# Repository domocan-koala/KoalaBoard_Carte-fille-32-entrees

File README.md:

# Carte fille 32 entrées

/3D_dessus.jpg)

Carte fille compatible [KoalaBoard](https://github.com/domocan-koala/KoalaBoard) pour relier 32 boutons-poussoirs avec votre système domotique [Domocan Master Édition](https://www.abcelectronique.com/bigonoff/forum/forumdisplay.php?fid=22).

## Historique
	
	* 23/02/18 V1.0 : Première version mise en ligne

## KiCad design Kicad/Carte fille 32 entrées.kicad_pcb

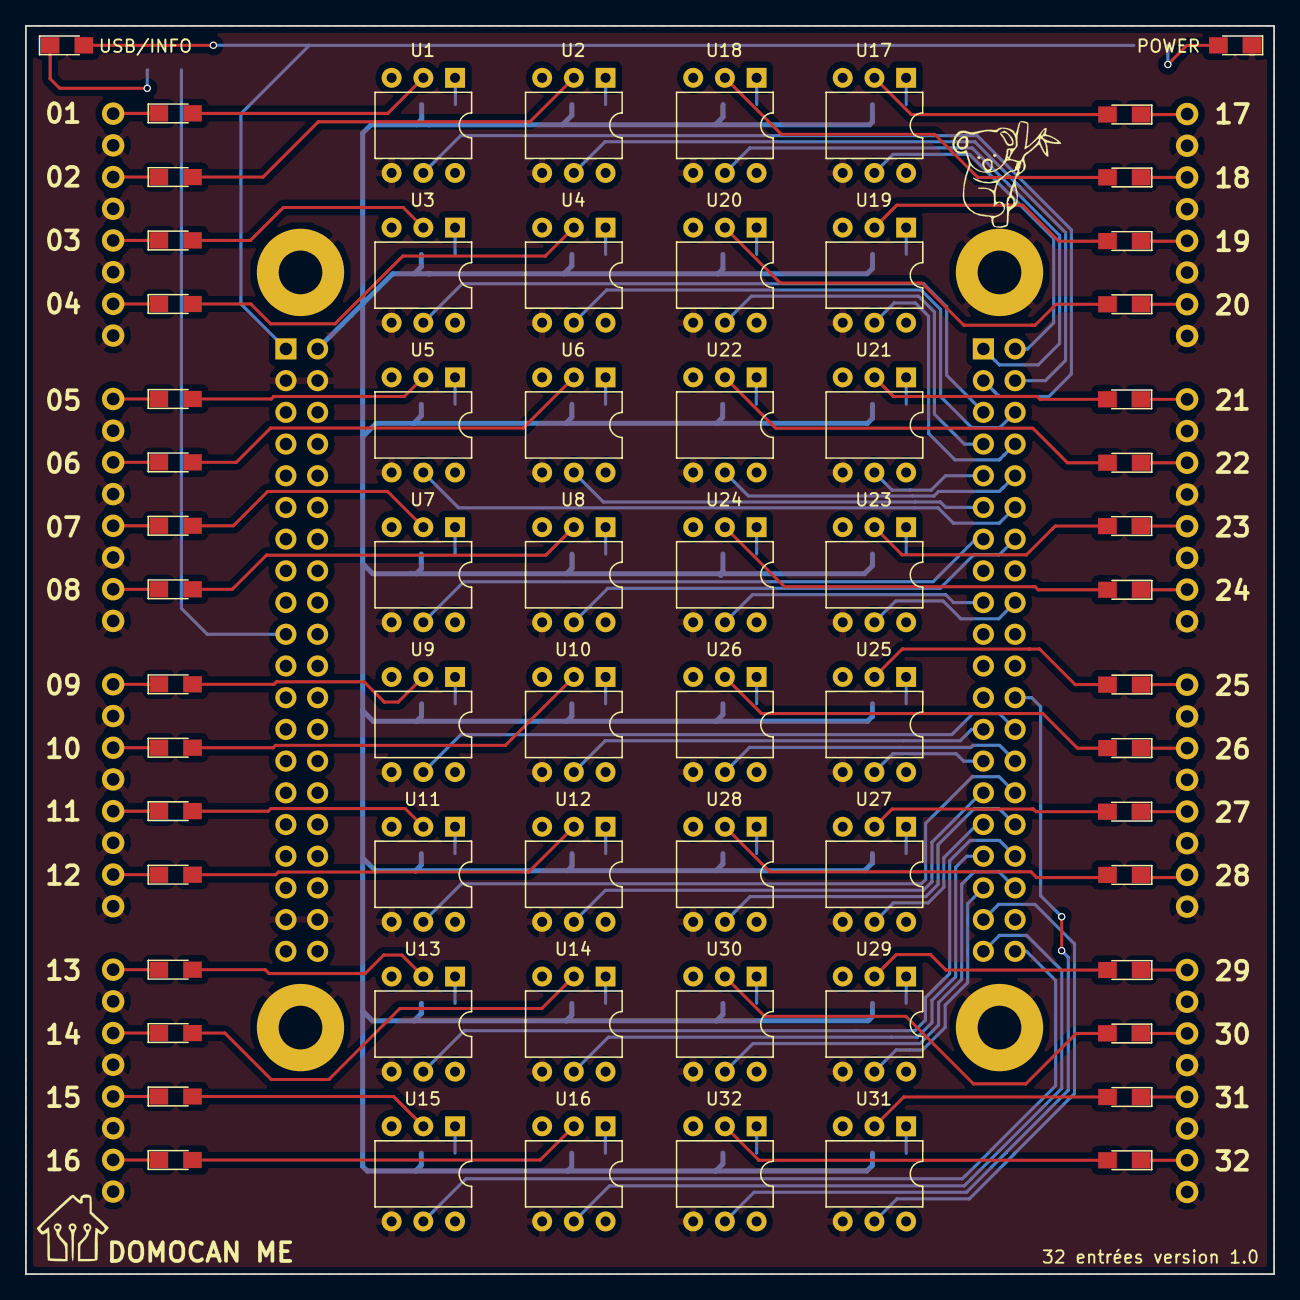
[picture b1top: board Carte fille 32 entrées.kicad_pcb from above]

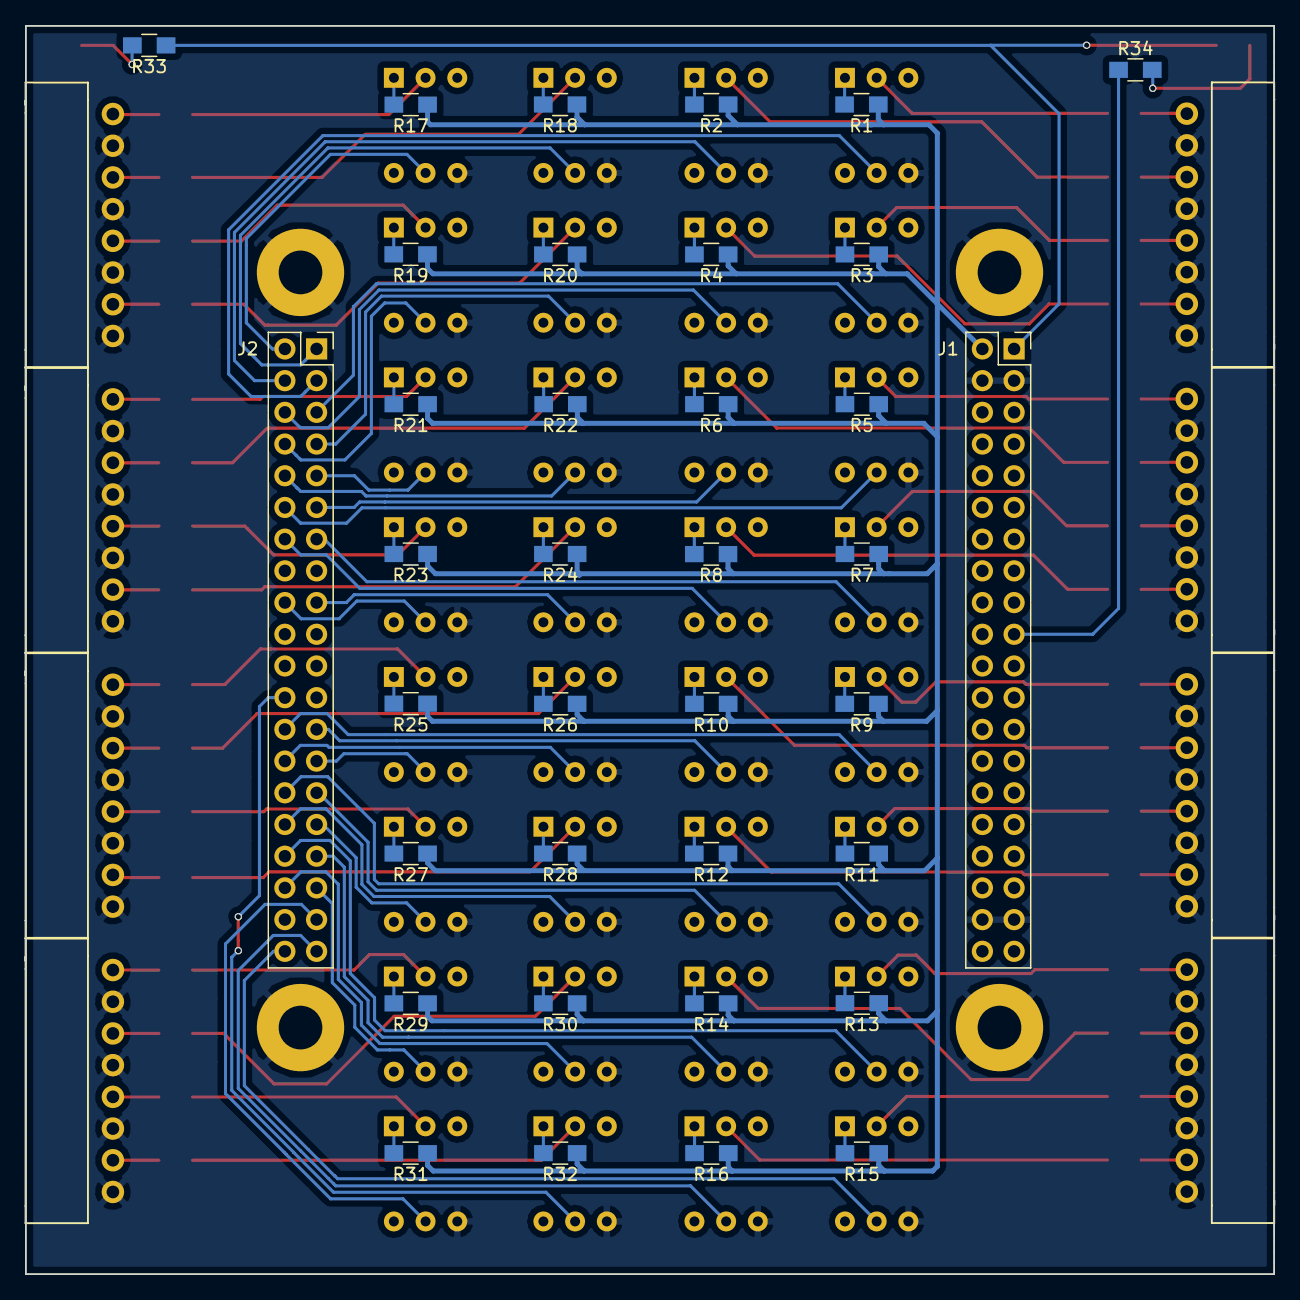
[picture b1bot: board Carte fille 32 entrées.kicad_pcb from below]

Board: 2 copper layers, 100.0 x 100.0 mm, 116 parts (44 on the bottom side), 134 nets.

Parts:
D1, D2, D3, D4, D5, D6, D7, D8, D9, D10, D11, D12, D13, D14, D15, D16, D17, D18, D19, D20, D21, D22, D23, D24, D25, D26, D27, D28, D29, D30, D31, D32: LED; LED_0805_HandSoldering
D33: POWER; LED_0805_HandSoldering
D34: USB/INFO; LED_0805_HandSoldering
J1, J2: Conn_02x20_Odd_Even; Socket_Strip_Straight_2x20_Pitch2.54mm
J3, J4, J5, J6, J7, J8, J9, J10: Conn_01x08; Pin_Header_Angled_1x08
J11, J12, J13, J14: Conn_01x01; MountingHole_3.5mm_Pad
J15: Logo Domocan; usb
J16: Logo Koala; koala
R1, R2, R3, R4, R5, R6, R7, R8, R9, R10, R11, R12, R13, R14, R15, R16, R17, R18, R19, R20, R21, R22, R23, R24, R25, R26, R27, R28, R29, R30, R31, R32: 220R; R_0805_HandSoldering
R33, R34: 470R; R_0805_HandSoldering
U1, U2, U3, U4, U5, U6, U7, U8, U9, U10, U11, U12, U13, U14, U15, U16, U17, U18, U19, U20, U21, U22, U23, U24, U25, U26, U27, U28, U29, U30, U31, U32: CNY17; DIP-6_W7.62mm

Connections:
+3V3: D34.2, J1.1, R33.1
+5V: J1.2, R1.1, R2.1, R3.1, R4.1, R5.1, R6.1, R7.1, R8.1, R9.1, R10.1, R11.1, R12.1, R13.1, R14.1, R15.1, R16.1, R17.1, R18.1, R19.1, R20.1, R21.1, R22.1, R23.1, R24.1, R25.1, R26.1, R27.1, R28.1, R29.1, R30.1, R31.1, R32.1
GND: D33.1, J1.3, J1.4, J1.37, J1.38, J3.2, J3.4, J3.6, J3.8, J4.2, J4.4, J4.6, J4.8, J5.2, J5.4, J5.6, J5.8, J6.2, J6.4, J6.6, J6.8, J7.1, J7.3, J7.5, J7.7, J8.1, J8.3, J8.5, J8.7, J9.1, J9.3, J9.5, J9.7, J10.1, J10.3, J10.5, J10.7, J11.1, J12.1, J13.1, J14.1, U1.4, U2.4, U3.4, U4.4, U5.4, U6.4, U7.4, U8.4, U9.4, U10.4, U11.4, U12.4, U13.4, U14.4, U15.4, U16.4, U17.4, U18.4, U19.4, U20.4, U21.4, U22.4, U23.4, U24.4, U25.4, U26.4, U27.4, U28.4, U29.4, U30.4, U31.4, U32.4
IN-01: D1.1, J3.1
IN-02: D2.1, J3.3
IN-03: D3.1, J3.5
IN-04: D4.1, J3.7
IN-05: D5.1, J4.1
IN-06: D6.1, J4.3
IN-07: D7.1, J4.5
IN-08: D8.1, J4.7
IN-09: D9.1, J5.1
IN-10: D10.1, J5.3
IN-11: D11.1, J5.5
IN-12: D12.1, J5.7
IN-13: D13.1, J6.1
IN-14: D14.1, J6.3
IN-15: D15.1, J6.5
IN-16: D16.1, J6.7
IN-17: D17.1, J7.8
IN-18: D18.1, J7.6
IN-19: D19.1, J7.4
IN-20: D20.1, J7.2
IN-21: D21.1, J8.8
IN-22: D22.1, J8.6
IN-23: D23.1, J8.4
IN-24: D24.1, J8.2
IN-25: D25.1, J9.8
IN-26: D26.1, J9.6
IN-27: D27.1, J9.4
IN-28: D28.1, J9.2
IN-29: D29.1, J10.8
IN-30: D30.1, J10.6
IN-31: D31.1, J10.4
IN-32: D32.1, J10.2
J2_P0.02: J2.2, U17.5
J2_P0.03: J2.1, U18.5
J2_P0.06: J2.17, U24.5
J2_P0.07: J2.18, U23.5
J2_P0.15: J2.31, U27.5
J2_P0.16: J2.30, U11.5
J2_P0.17: J2.32, U28.5
J2_P0.18: J2.33, U14.5
J2_P0.19: J2.34, U13.5
J2_P0.20: J2.35, U29.5
J2_P0.21: J2.36, U30.5
J2_P0.22: J2.37, U31.5
J2_P1.00: J2.3, U1.5
J2_P1.01: J2.4, U2.5
J2_P1.04: J2.5, U3.5
J2_P1.08: J2.6, U4.5
J2_P1.09: J2.7, U20.5
J2_P1.10: J2.8, U19.5
J2_P1.14: J2.9, U21.5
J2_P1.15: J2.10, U22.5
J2_P1.16: J2.11, U6.5
J2_P1.17: J2.12, U5.5
J2_P2.03: J2.24, U32.5
J2_P2.04: J2.25, U10.5
J2_P2.05: J2.26, U9.5
J2_P2.06: J2.27, U25.5
J2_P2.07: J2.28, U26.5
J2_P2.08: J2.29, U12.5
J2_P2.11: J2.39, U16.5
J2_P2.12: J2.40, U15.5
J2_P4.28: J2.14, U8.5
J2_P4.29: J2.13, U7.5
unnamed: D1.2, U1.2
unnamed: D2.2, U2.2
unnamed: D3.2, U3.2
unnamed: D4.2, U4.2
unnamed: D5.2, U5.2
unnamed: D6.2, U6.2
unnamed: D7.2, U7.2
unnamed: D8.2, U8.2
unnamed: D9.2, U9.2
unnamed: D10.2, U10.2
unnamed: D11.2, U11.2
unnamed: D12.2, U12.2
unnamed: D13.2, U13.2
unnamed: D14.2, U14.2
unnamed: D15.2, U15.2
unnamed: D16.2, U16.2
unnamed: D17.2, U17.2
unnamed: D18.2, U18.2
unnamed: D19.2, U19.2
unnamed: D20.2, U20.2
unnamed: D21.2, U21.2
unnamed: D22.2, U22.2
unnamed: D23.2, U23.2
unnamed: D24.2, U24.2
unnamed: D25.2, U25.2
unnamed: D26.2, U26.2
unnamed: D27.2, U27.2
unnamed: D28.2, U28.2
unnamed: D29.2, U29.2
unnamed: D30.2, U30.2
unnamed: D31.2, U31.2
unnamed: D32.2, U32.2
unnamed: D33.2, R33.2
unnamed: D34.1, R34.2
unnamed: J1.19, R34.1
unnamed: R1.2, U1.1
unnamed: R2.2, U2.1
unnamed: R3.2, U3.1
unnamed: R4.2, U4.1
unnamed: R5.2, U5.1
unnamed: R6.2, U6.1
unnamed: R7.2, U7.1
unnamed: R8.2, U8.1
unnamed: R9.2, U9.1
unnamed: R10.2, U10.1
unnamed: R11.2, U11.1
unnamed: R12.2, U12.1
unnamed: R13.2, U13.1
unnamed: R14.2, U14.1
unnamed: R15.2, U15.1
unnamed: R16.2, U16.1
unnamed: R17.2, U17.1
unnamed: R18.2, U18.1
unnamed: R19.2, U19.1
unnamed: R20.2, U20.1
unnamed: R21.2, U21.1
unnamed: R22.2, U22.1
unnamed: R23.2, U23.1
unnamed: R24.2, U24.1
unnamed: R25.2, U25.1
unnamed: R26.2, U26.1
unnamed: R27.2, U27.1
unnamed: R28.2, U28.1
unnamed: R29.2, U29.1
unnamed: R30.2, U30.1
unnamed: R31.2, U31.1
unnamed: R32.2, U32.1

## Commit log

2018-02-23 Première mise en ligne
    Carte fille 32 entrées compatible KoalaBoard pour le système domotique
    Domocan
2018-02-27 Correction vue 3D
2018-02-28 Organisation des fichiers
    Nouvelle organisation suite à la version CMS de la même carte en cours
    de création
2018-02-28 Documentation
    Ajout de l'image
